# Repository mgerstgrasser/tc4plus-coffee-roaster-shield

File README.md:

# tc4plus-coffee-roaster-shield

The TC4+ is an Arduino shield designed for temperature measurement, logging and control applications. Both the original TC4 and the TC4+ are designed with coffee roasting applications in mind, but work for a wide range of applications. The TC4+ is an extension of the TC4 shield, adding useful extra such as DC fan motor control and a header for an optional Bluetooth module.

**Features**

- 4-channel, high-resolution thermocouple interface.

- 2-channel SSR drivers for AC loads, and single-channel DC driver for DC fan motors.

- Full compatibility with TC4-based Arduino sketches and established software ecosystem.
- Highly simplified control of popcorn machine based roasters: On-board voltage regulator and DC PWM driver allow popcorn roaster setup with just the TC4+, a single DC power supply and one solid state relay.
- Designed with a high degree of flexibility in mind. Wide range of voltage regulators supported; extra I2C headers for displays and other peripherals; retains all TC4 features and full Arduino pinout.
- Wireless control with optional Bluetooth module. 

**References**
- [Tindie](https://www.tindie.com/products/15798/)
- [Official website](https://coffee.gerstgrasser.net/)
- [Discussion on homeroasters.org](https://forum.homeroasters.org/forum/viewthread.php?forum_id=133&thread_id=5562&pid=65572)
- [TC4 shield and software](https://github.com/greencardigan/TC4-shield)

**License**
These files are available under a [Attribution-NonCommercial-ShareAlike 4.0 International (CC BY-NC-SA 4.0)](https://creativecommons.org/licenses/by-nc-sa/4.0/) license.

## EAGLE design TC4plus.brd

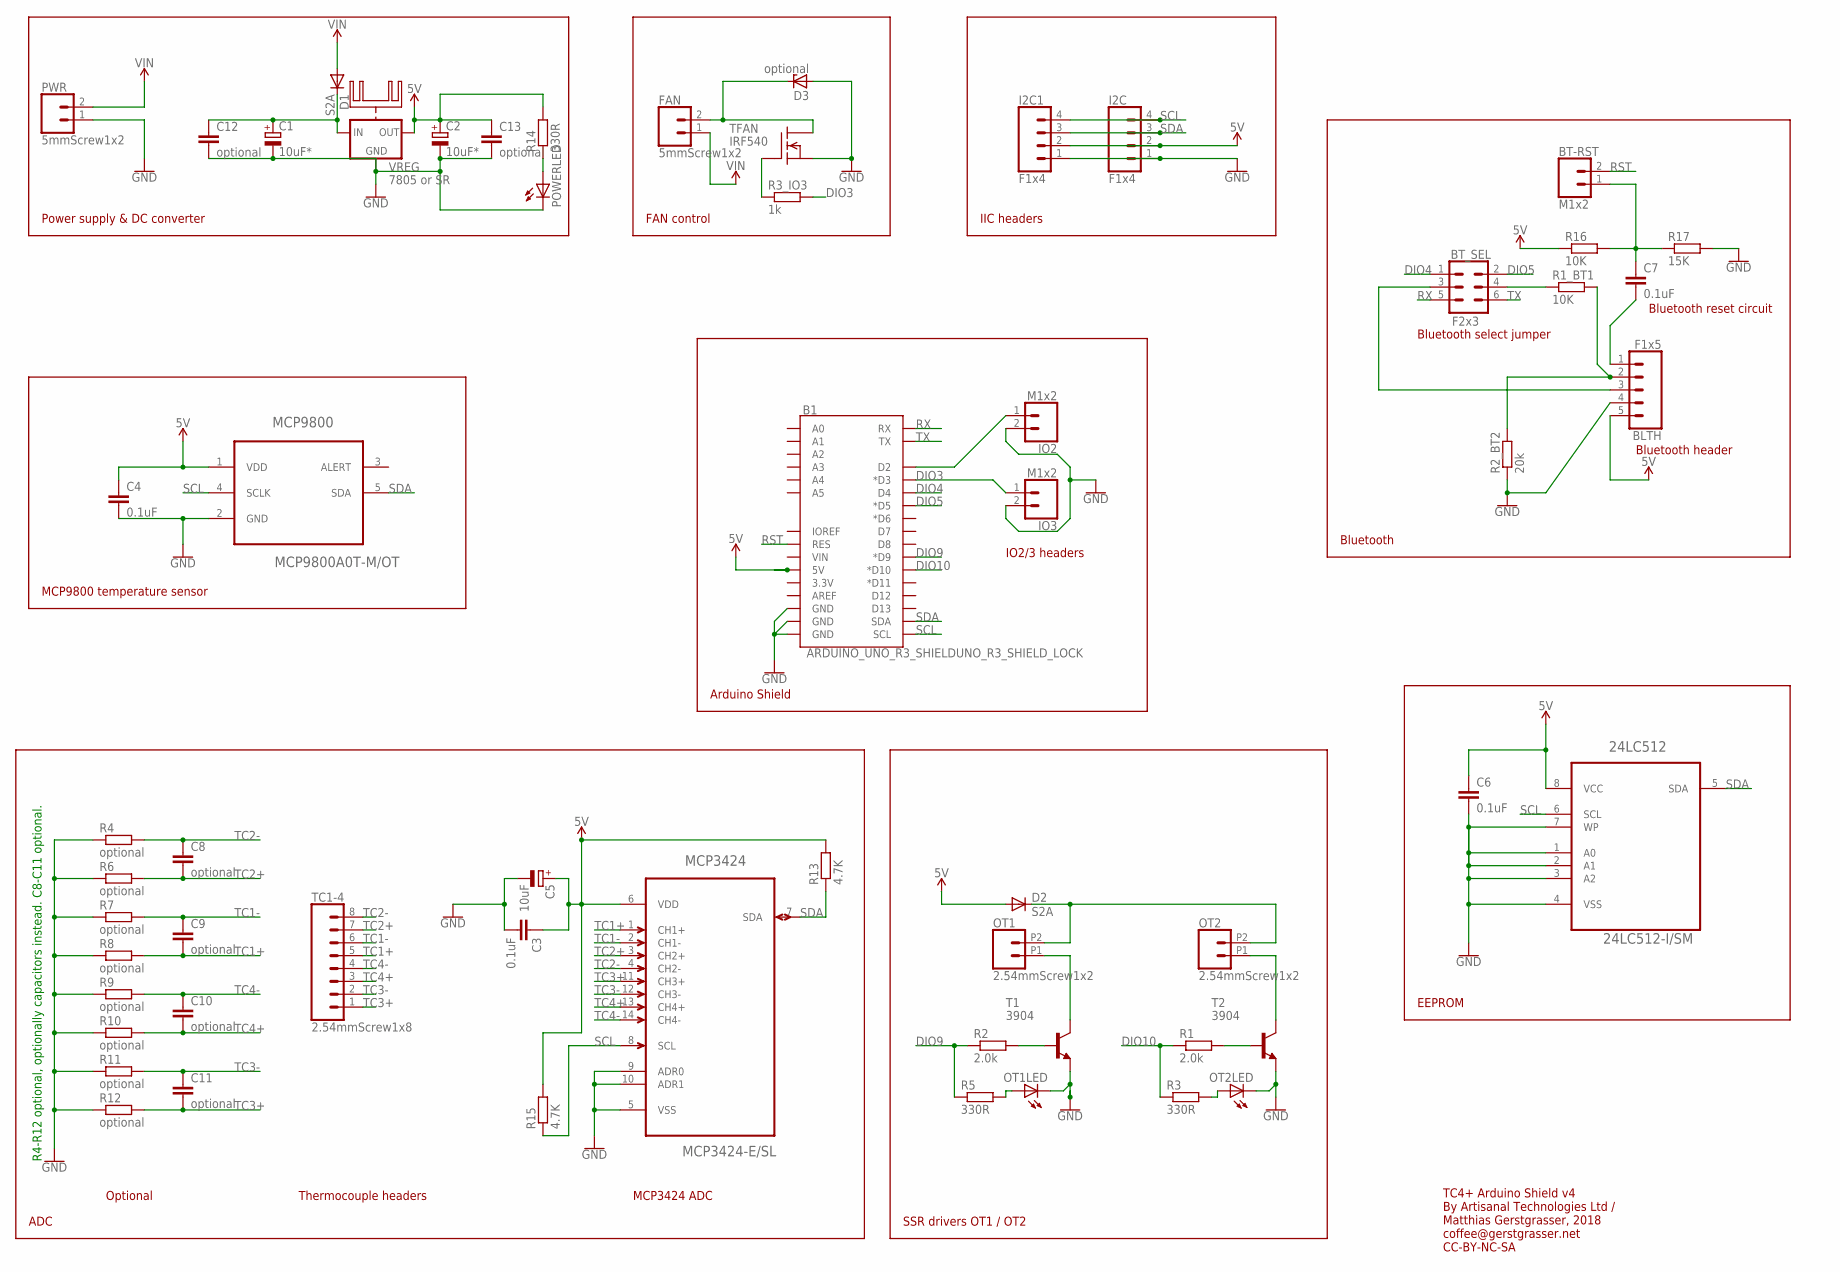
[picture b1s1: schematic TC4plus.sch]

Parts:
24LC512: 24LC512-I/SM; SOIC127P794X203-8N
B1: ARDUINO_UNO_R3_SHIELDUNO_R3_SHIELD_LOCK; UNO_R3_SHIELD_LOCK
BLTH: F1x5; 1X05_LOCK
BT-RST: M1x2; 1X02
BT_SEL: F2x3; 2X3
C1, C2: 10uF*; E2-5
C3, C4, C6, C7: 0.1uF; C0603
C5: 10uF; A/3216-18R
C8, C9, C10, C11: optional; C0603
C12, C13: optional; C025-025X050
D1, D2: S2A; DO214AA
D3: optional; SMB
FAN: 5mmScrew1x2; SCREWTERMINAL-5MM-2
I2C, I2C1: F1x4; 1X04_LOCK
IO2, IO3: M1x2; 1X02
MCP3424: MCP3424-E/SL; SOIC127P600X175-14N
MCP9800: MCP9800A0T-M/OT; SOT95P280X145-5N
OT1, OT2: 2.54mmScrew1x2; 1X02_2.54_SCREWTERM
OT1LED, OT2LED: LEDCHIP-LED0603; CHIP-LED0603
POWERLED: LEDCHIP-LED0603; CHIP-LED0603
PWR: 5mmScrew1x2; SCREWTERMINAL-5MM-2
R1, R2: 2.0k; R0603
R1_BT1, R16: 10K; R0603
R2_BT2: 20k; R0603
R3, R5, R14: 330R; R0603
R3_IO3: 1k; R0603
R4, R6, R7, R8, R9, R10, R11, R12: optional; R0603
R13, R15: 4.7K; R0603
R17: 15K; R0603
T1, T2: 3904; SOT23-BEC
TC1-4: 2.54mmScrew1x8; 1X08
TFAN: IRF540; TO220
VREG: 7805 or SR; 78XXH

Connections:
5V: 24LC512.8 (VCC), B1.5V, BLTH.5, C2.+, C3.1, C4.1, C5.+, C6.1, C13.1, D2.A, I2C.2, I2C1.2, MCP3424.6 (VDD), MCP9800.1 (VDD), R13.2, R14.2, R15.2, R16.1, VREG.OUT
DC-: D3.C, FAN.2, TFAN.2 (D)
DIO3: B1.D3 (*D3), IO3.1, R3_IO3.2
DIO4: B1.D4, BT_SEL.1
DIO5: B1.D5 (*D5), BT_SEL.2
DIO9: B1.D9 (*D9), R2.1, R5.1
DIO10: B1.D10 (*D10), R1.1, R3.1
GND: 24LC512.1 (A0), 24LC512.2 (A1), 24LC512.3 (A2), 24LC512.4 (VSS), 24LC512.7 (WP), B1.GND@0 (GND), B1.GND@1 (GND), B1.GND@2 (GND), BLTH.4, C1.-, C2.-, C3.2, C4.2, C5.-, C6.2, C12.2, C13.2, D3.A, I2C.1, I2C1.1, IO2.2, IO3.2, MCP3424.5 (VSS), MCP3424.9 (ADR0), MCP3424.10 (ADR1), MCP9800.2 (GND), OT1LED.C, OT2LED.C, POWERLED.C, PWR.1, R2_BT2.1, R4.1, R6.1, R7.1, R8.1, R9.1, R10.1, R11.1, R12.1, R17.2, T1.E, T2.E, TFAN.3 (S), VREG.GND
unnamed: R2.2, T1.B
unnamed: BLTH.2, R1_BT1.2, R2_BT2.2
unnamed: BT_SEL.4, R1_BT1.1
unnamed: BLTH.3, BT_SEL.3
unnamed: R1.2, T2.B
unnamed: R3_IO3.1, TFAN.1 (G)
unnamed: BLTH.1, C7.2
unnamed: OT2LED.A, R3.2
unnamed: POWERLED.A, R14.1
unnamed: OT1LED.A, R5.2
unnamed: BT-RST.1, C7.1, R16.2, R17.1
unnamed: C1.+, C12.1, D1.C, VREG.IN
unnamed: B1.D2, IO2.1
OT1-: OT1.P1 (1), T1.C
OT2-: OT2.P1 (1), T2.C
OT12+: D2.C, OT1.P2 (2), OT2.P2 (2)
RST: B1.RES, BT-RST.2
RX: B1.RX, BT_SEL.5
SCL: 24LC512.6 (SCL), B1.SCL, I2C.4, I2C1.4, MCP3424.8 (SCL), MCP9800.4 (SCLK), R15.1
SDA: 24LC512.5 (SDA), B1.SDA, I2C.3, I2C1.3, MCP3424.7 (SDA), MCP9800.5 (SDA), R13.1
TC1+: C9.2, MCP3424.1 (CH1+), R8.2, TC1-4.5
TC1-: C9.1, MCP3424.2 (CH1-), R7.2, TC1-4.6
TC2+: C8.2, MCP3424.3 (CH2+), R6.2, TC1-4.7
TC2-: C8.1, MCP3424.4 (CH2-), R4.2, TC1-4.8
TC3+: C11.2, MCP3424.11 (CH3+), R12.2, TC1-4.1
TC3-: C11.1, MCP3424.12 (CH3-), R11.2, TC1-4.2
TC4+: C10.2, MCP3424.13 (CH4+), R10.2, TC1-4.3
TC4-: C10.1, MCP3424.14 (CH4-), R9.2, TC1-4.4
TX: B1.TX, BT_SEL.6
VIN: D1.A, FAN.1, PWR.2

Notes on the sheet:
R4-R12 optional, optionally capacitors instead. C8-C11 optional.
Power supply & DC converter
FAN control
IIC headers
MCP9800 temperature sensor
Arduino Shield
IO2/3 headers
Bluetooth
Bluetooth header
Bluetooth reset circuit
Bluetooth select jumper
EEPROM
SSR drivers OT1 / OT2
Thermocouple headers
MCP3424 ADC
Optional
ADC
TC4+ Arduino Shield v4 By Artisanal Technologies Ltd / Matthias Gerstgrasser, 2018 coffee@gerstgrasser.net CC-BY-NC-SA

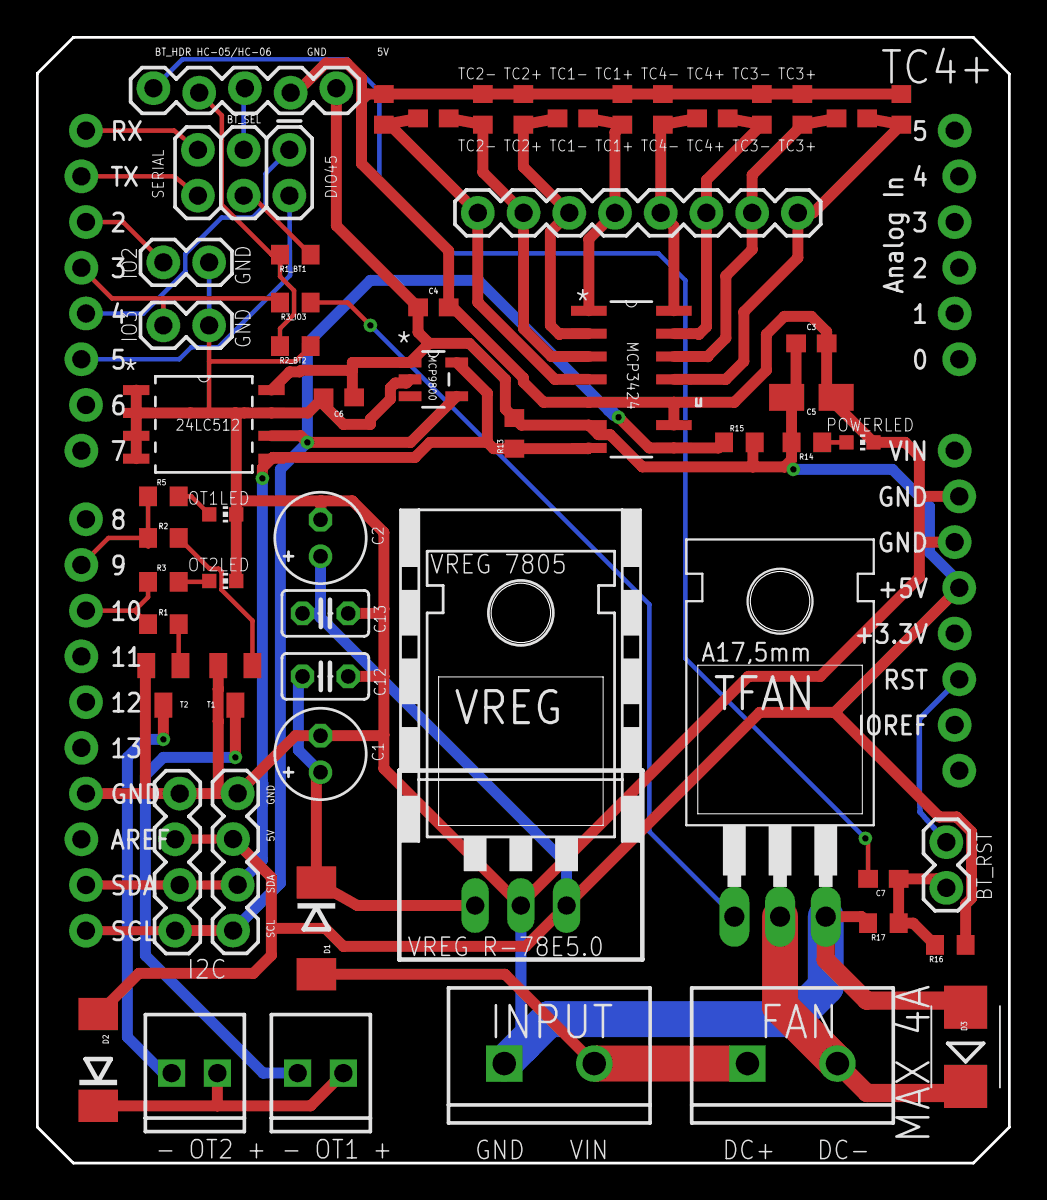
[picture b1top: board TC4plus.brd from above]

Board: 2 copper layers, 54.0 x 62.5 mm, 59 parts (0 on the bottom side), 38 nets.

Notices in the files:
parts and their libraries:
SparkFun-Boards: Licensing: Creative Commons ShareAlike 4.0 International - https://creativecommons.org/licenses/by-sa/4.0
